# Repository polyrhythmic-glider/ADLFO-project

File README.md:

# Adolfo

Piattaforma Eurorack programmabile da 20 HP: quattro ingressi universali,
quattro uscite universali e quattro porte di controllo bidirezionali.
Quattro encoder con click, quattro tasti e OLED. Alimentazione Eurorack IDC10 ±12 V.

| Porta | Funzioni previste |
| --- | --- |
| IN1–4 | audio, CV, gate, trigger |
| OUT1–4 | audio, CV, envelope, LFO, gate, trigger |
| CTRL1–4 | CV/gate/trigger, ingresso oppure uscita |

## Due stati distinti

- **[Adolfo/](Adolfo/README.md)** è il firmware funzionante del prototipo
  Daisy + DAC Adafruit MCP4728, rinominato da DaisyMonoEnvelope. Motori e
  comandi sono conservati; il nome del binario diventa `Adolfo.bin`.
- **[hardware/pcb/](hardware/pcb/README.md)** contiene la nuova revisione D:
  schema gerarchico, filtri analogici, supervisione e due PCB con conversione
  esterna DC coupled. I rapporti CAD sono in `hardware/pcb/output/`.
  Il firmware del prototipo non pilota questa scheda: backend e qualifica
  al banco restano necessari prima dell'uso.

La [revisione completa del branch 20 HP](hardware/pcb/DESIGN_REVIEW_20HP.md)
individua inoltre blocchi di progetto su sequenziamento dell'ADC, supervisione
5 V e backend SPI/DMA. Lo stato CAD superato non autorizza il rilascio hardware.

Le vecchie PCB 24/20 HP per il solo AD/LFO, le diagnostiche separate e gli
schemi breadboard superati sono stati rimossi dal branch. La storia Git conserva
il materiale precedente; [pulizia e conservazione](docs/CLEANUP.md).

## Da dove iniziare

1. [Architettura e compromessi](hardware/pcb/ARCHITECTURE.md).
2. [Componenti da aggiungere e materiale da riutilizzare](hardware/pcb/PARTS.md).
3. [Cablaggio del prototipo preservato](docs/PROTOTYPE.md).
4. [Lavoro restante prima della produzione](hardware/pcb/RELEASE_CHECKLIST.md).

## Generazione e controlli

Python 3 con venv, compilatore C++ per i test locali. I file hardware sono
verificati con KiCad 10.0.7. Per aprirli e ricostruirli seguire le
[istruzioni hardware](hardware/pcb/README.md): `make pcb` da solo rigenera
il posizionamento e sostituisce le piste; non completa il processo di routing.

```sh
python3 -m venv .venv
.venv/bin/python -m pip install -r hardware/pcb/requirements.txt
make check
make test
```

Per il firmware del prototipo servono libDaisy/DaisySP e `arm-none-eabi`:

```sh
make -C Adolfo
make -C Adolfo test
```

I percorsi delle librerie restano sovrascrivibili con `LIBDAISY_DIR` e
`DAISYSP_DIR`. Nessun comando di generazione carica firmware o ordina una PCB.

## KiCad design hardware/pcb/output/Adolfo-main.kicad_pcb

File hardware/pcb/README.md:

# Adolfo universal — revisione D

Due PCB per un modulo Eurorack da 20 HP: 4 IN, 4 OUT, 4 CTRL bidirezionali,
quattro encoder con click, quattro tasti e OLED. La revisione D completa lo schema
funzionale, i filtri, l'alimentazione, la supervisione e le piste delle due schede.

**Alimentazione dal connettore Eurorack IDC10, senza USB-C:** il +12 V del case,
attraverso fusibile e protezione di polarità, alimenta il convertitore RECOM a 5 V.
Questi 5 V alimentano VIN della Daisy (pin 39) e il ramo analogico filtrato;
la Daisy genera i 3,3 V. Il −12 V alimenta il ramo analogico negativo.
Non serve il +5 V del case. Lasciare scollegata la USB-C della Seed nel modulo
assemblato: la Seed standard può alimentarsi da USB e il carrier non interrompe
quel percorso interno. Per programmare via USB, estrarre la Seed dal carrier
con il case spento e scollegato.

**Rilascio bloccato dalla [revisione completa](DESIGN_REVIEW_20HP.md):** sequenziamento
AVCC/VDRIVE dell'ADC, margini del monitor 5 V e backend SPI/DMA da riprogettare.
Il superamento dei controlli CAD non risolve questi problemi elettrici.
I datasheet consultati sono conservati localmente in `datasheets/`;
`references.json` registra le fonti e la revisione riporta le basi di verifica.

Aprire con **KiCad 10**:

- [output/Adolfo-main.kicad_pro](output/Adolfo-main.kicad_pro): progetto principale, schema gerarchico e PCB a quattro strati.
- [output/Adolfo-panel.kicad_pro](output/Adolfo-panel.kicad_pro): comandi, jack, display e PCB frontale a due strati.
- [output/index.html](output/index.html): viste 2D e distinta ricercabile.
- [output/front.svg](output/front.svg): frontale aggiornato con display centrale.
- [output/drill.svg](output/drill.svg) e [DXF](output/panel-concept.dxf): dima e taglio nominali aggiornati.
- [output/bom.csv](output/bom.csv): valori, codici scelti, lato e coordinate.
- [output/validation.json](output/validation.json): esito dei controlli sulla revisione salvata.

Le librerie locali sono incluse: tenere tutta la cartella `output` insieme.
Le viste correnti sono SVG; le vecchie copie PNG/PDF della revisione C e la
netlist unica del vecchio progetto sono state rimosse. Le netlist native correnti
sono `Adolfo-main.net` e `Adolfo-panel.net`.
In KiCad, dal gestore progetto aprire lo schema oppure l'editor PCB. Le piste
visibili nell'editor sono rame reale del file PCB. Non è inclusa un'immagine 3D.

La qualifica CAD comprende ERC, DRC, collegamenti mancanti e parità schema/PCB,
oltre al confronto pin per pin fra sorgente, netlist compilata e schede salvate.
I rapporti nativi sono `erc-main.json`, `erc-panel.json`, `drc-main.json` e
`drc-panel.json`. `native-checks.json` ne registra le impronte SHA256, insieme
ai file CAD verificati: una modifica richiede nuovi controlli.

**Prototipo ingegneristico, non ancora qualificato al banco.** Il firmware in
`Adolfo/` pilota il vecchio prototipo con MCP4728; per questa PCB occorre il
backend ADC/DAC, il filtro digitale e il collaudo indicato nella
[lista di qualifica](RELEASE_CHECKLIST.md). Non confondere DRC pulito con misura
di rumore, stabilità, termica o precisione sotto carico.

[Architettura](ARCHITECTURE.md) · [Componenti e montaggio](PARTS.md)

## Rigenerazione

La generazione iniziale **sostituisce le schede e rimuove lo sbroglio esistente**.
Usarla solo quando si intende ricostruire la revisione, conservando prima il lavoro.
Servono Python con `requirements.txt`, KiCad 10 e Java 21 con
[Freerouting 2.0.1](https://github.com/freerouting/freerouting/releases/tag/v2.0.1).
Il JAR va in `.venv/tools/freerouting-2.0.1.jar` oppure in `FREEROUTING_JAR`.
Il router lavora localmente, con telemetria disattivata (`-da`).

PowerShell, dalla radice del repository:

```powershell
& .\.venv\Scripts\python.exe -X utf8 hardware/pcb/build.py
& 'C:\Program Files\KiCad\10.0\bin\python.exe' -X utf8 hardware/pcb/board_setup.py
& 'C:\Program Files\KiCad\10.0\bin\python.exe' -X utf8 hardware/pcb/route.py
& .\.venv\Scripts\python.exe -X utf8 hardware/pcb/native_checks.py
& 'C:\Program Files\KiCad\10.0\bin\python.exe' -X utf8 hardware/pcb/board_setup.py audit
& .\.venv\Scripts\python.exe -X utf8 hardware/pcb/validate.py
```

Per ricontrollare i file esistenti eseguire solo gli ultimi tre comandi.
`build.py` genera schema, impronte, distinta e posizionamento; `board_setup.py`
compila le netlist, applica i lati, configura gli strati, collega i pad di massa al piano con vie fisiche e crea i DSN. `route.py`
importa una nuova sessione solo dopo che il router termina correttamente.
`native_checks.py` richiede zero segnalazioni, senza esclusioni DRC, ed esporta quattro viste SVG del rame.
`validate.py` rifiuta rapporti o audit riferiti a file precedenti.

I file DSN/SES intermedi restano nella cartella ignorata `build/`. Il router
può lasciare connessioni aperte: la revisione consegnata comprende la chiusura
finale delle reti di alimentazione e supera i controlli. Dopo una rigenerazione
ricontrollare il risultato e completare eventuali reti residue in KiCad; il
validatore rifiuta uno sbroglio parziale. I file `.kicad_pcb` salvati sono il
risultato completo da aprire e modificare. I disegni meccanici hanno quote nominali e
richiedono una prova fisica prima di forare il frontale definitivo.

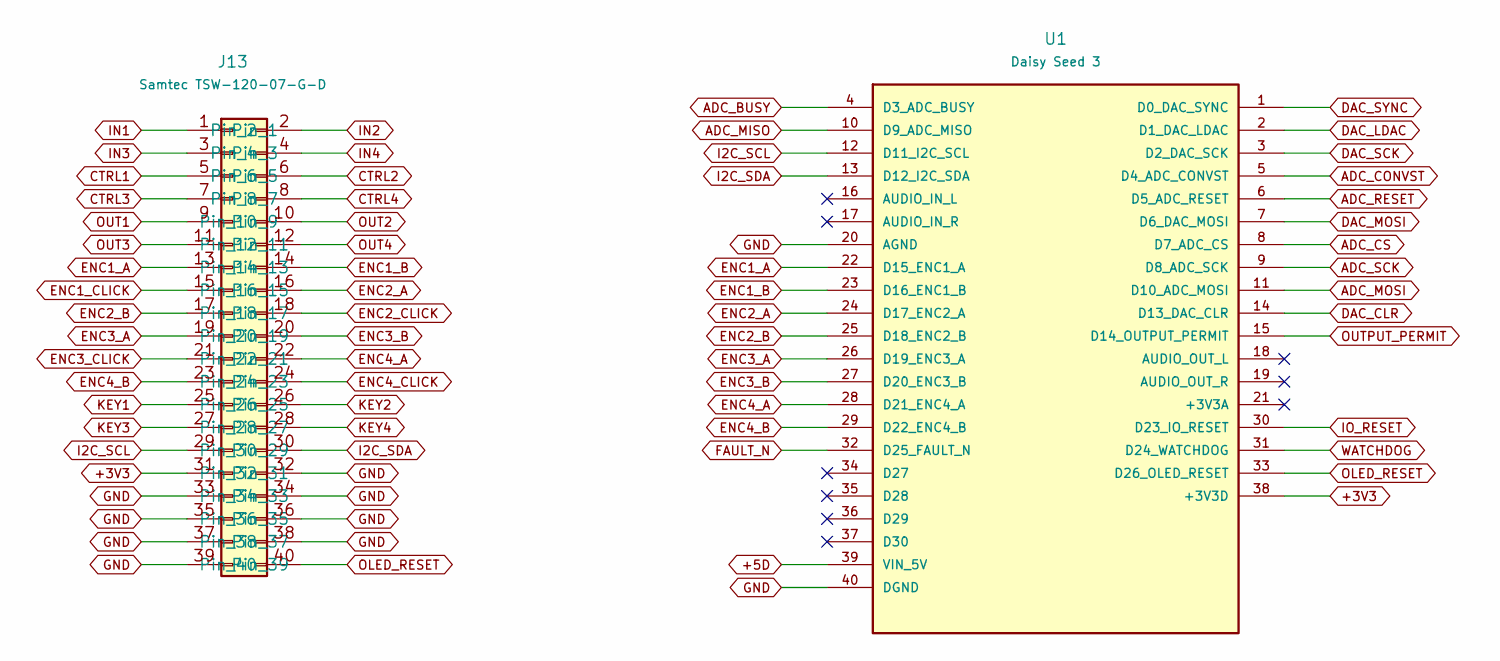
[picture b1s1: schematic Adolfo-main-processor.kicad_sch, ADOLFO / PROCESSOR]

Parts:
J13: Samtec TSW-120-07-G-D; header40
U1: Daisy Seed 3; seed

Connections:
+3V3: J13.31, U1.38 (+3V3D); also elsewhere on the board
+5D: U1.39 (VIN_5V); also elsewhere on the board
ADC_BUSY: U1.4 (D3_ADC_BUSY); also elsewhere on the board
ADC_CONVST: U1.5 (D4_ADC_CONVST); also elsewhere on the board
ADC_CS: U1.8 (D7_ADC_CS); also elsewhere on the board
ADC_MISO: U1.10 (D9_ADC_MISO); also elsewhere on the board
ADC_MOSI: U1.11 (D10_ADC_MOSI); also elsewhere on the board
ADC_RESET: U1.6 (D5_ADC_RESET); also elsewhere on the board
ADC_SCK: U1.9 (D8_ADC_SCK); also elsewhere on the board
CTRL1: J13.5; also elsewhere on the board
CTRL2: J13.6; also elsewhere on the board
CTRL3: J13.7; also elsewhere on the board
CTRL4: J13.8; also elsewhere on the board
DAC_CLR: U1.14 (D13_DAC_CLR); also elsewhere on the board
DAC_LDAC: U1.2 (D1_DAC_LDAC); also elsewhere on the board
DAC_MOSI: U1.7 (D6_DAC_MOSI); also elsewhere on the board
DAC_SCK: U1.3 (D2_DAC_SCK); also elsewhere on the board
DAC_SYNC: U1.1 (D0_DAC_SYNC); also elsewhere on the board
ENC1_A: J13.13, U1.22 (D15_ENC1_A); also elsewhere on the board
ENC1_B: J13.14, U1.23 (D16_ENC1_B); also elsewhere on the board
ENC1_CLICK: J13.15; also elsewhere on the board
ENC2_A: J13.16, U1.24 (D17_ENC2_A); also elsewhere on the board
ENC2_B: J13.17, U1.25 (D18_ENC2_B); also elsewhere on the board
ENC2_CLICK: J13.18; also elsewhere on the board
ENC3_A: J13.19, U1.26 (D19_ENC3_A); also elsewhere on the board
ENC3_B: J13.20, U1.27 (D20_ENC3_B); also elsewhere on the board
ENC3_CLICK: J13.21; also elsewhere on the board
ENC4_A: J13.22, U1.28 (D21_ENC4_A); also elsewhere on the board
ENC4_B: J13.23, U1.29 (D22_ENC4_B); also elsewhere on the board
ENC4_CLICK: J13.24; also elsewhere on the board
FAULT_N: U1.32 (D25_FAULT_N); also elsewhere on the board
GND: J13.32, J13.33, J13.34, J13.35, J13.36, J13.37, J13.38, J13.39, U1.20 (AGND), U1.40 (DGND); also elsewhere on the board
I2C_SCL: J13.29, U1.12 (D11_I2C_SCL); also elsewhere on the board
I2C_SDA: J13.30, U1.13 (D12_I2C_SDA); also elsewhere on the board
IN1: J13.1; also elsewhere on the board
IN2: J13.2; also elsewhere on the board
IN3: J13.3; also elsewhere on the board
IN4: J13.4; also elsewhere on the board
IO_RESET: U1.30 (D23_IO_RESET); also elsewhere on the board
KEY1: J13.25; also elsewhere on the board
KEY2: J13.26; also elsewhere on the board
KEY3: J13.27; also elsewhere on the board
KEY4: J13.28; also elsewhere on the board
OLED_RESET: J13.40, U1.33 (D26_OLED_RESET); also elsewhere on the board
OUT1: J13.9; also elsewhere on the board
OUT2: J13.10; also elsewhere on the board
OUT3: J13.11; also elsewhere on the board
OUT4: J13.12; also elsewhere on the board
OUTPUT_PERMIT: U1.15 (D14_OUTPUT_PERMIT); also elsewhere on the board
WATCHDOG: U1.31 (D24_WATCHDOG); also elsewhere on the board

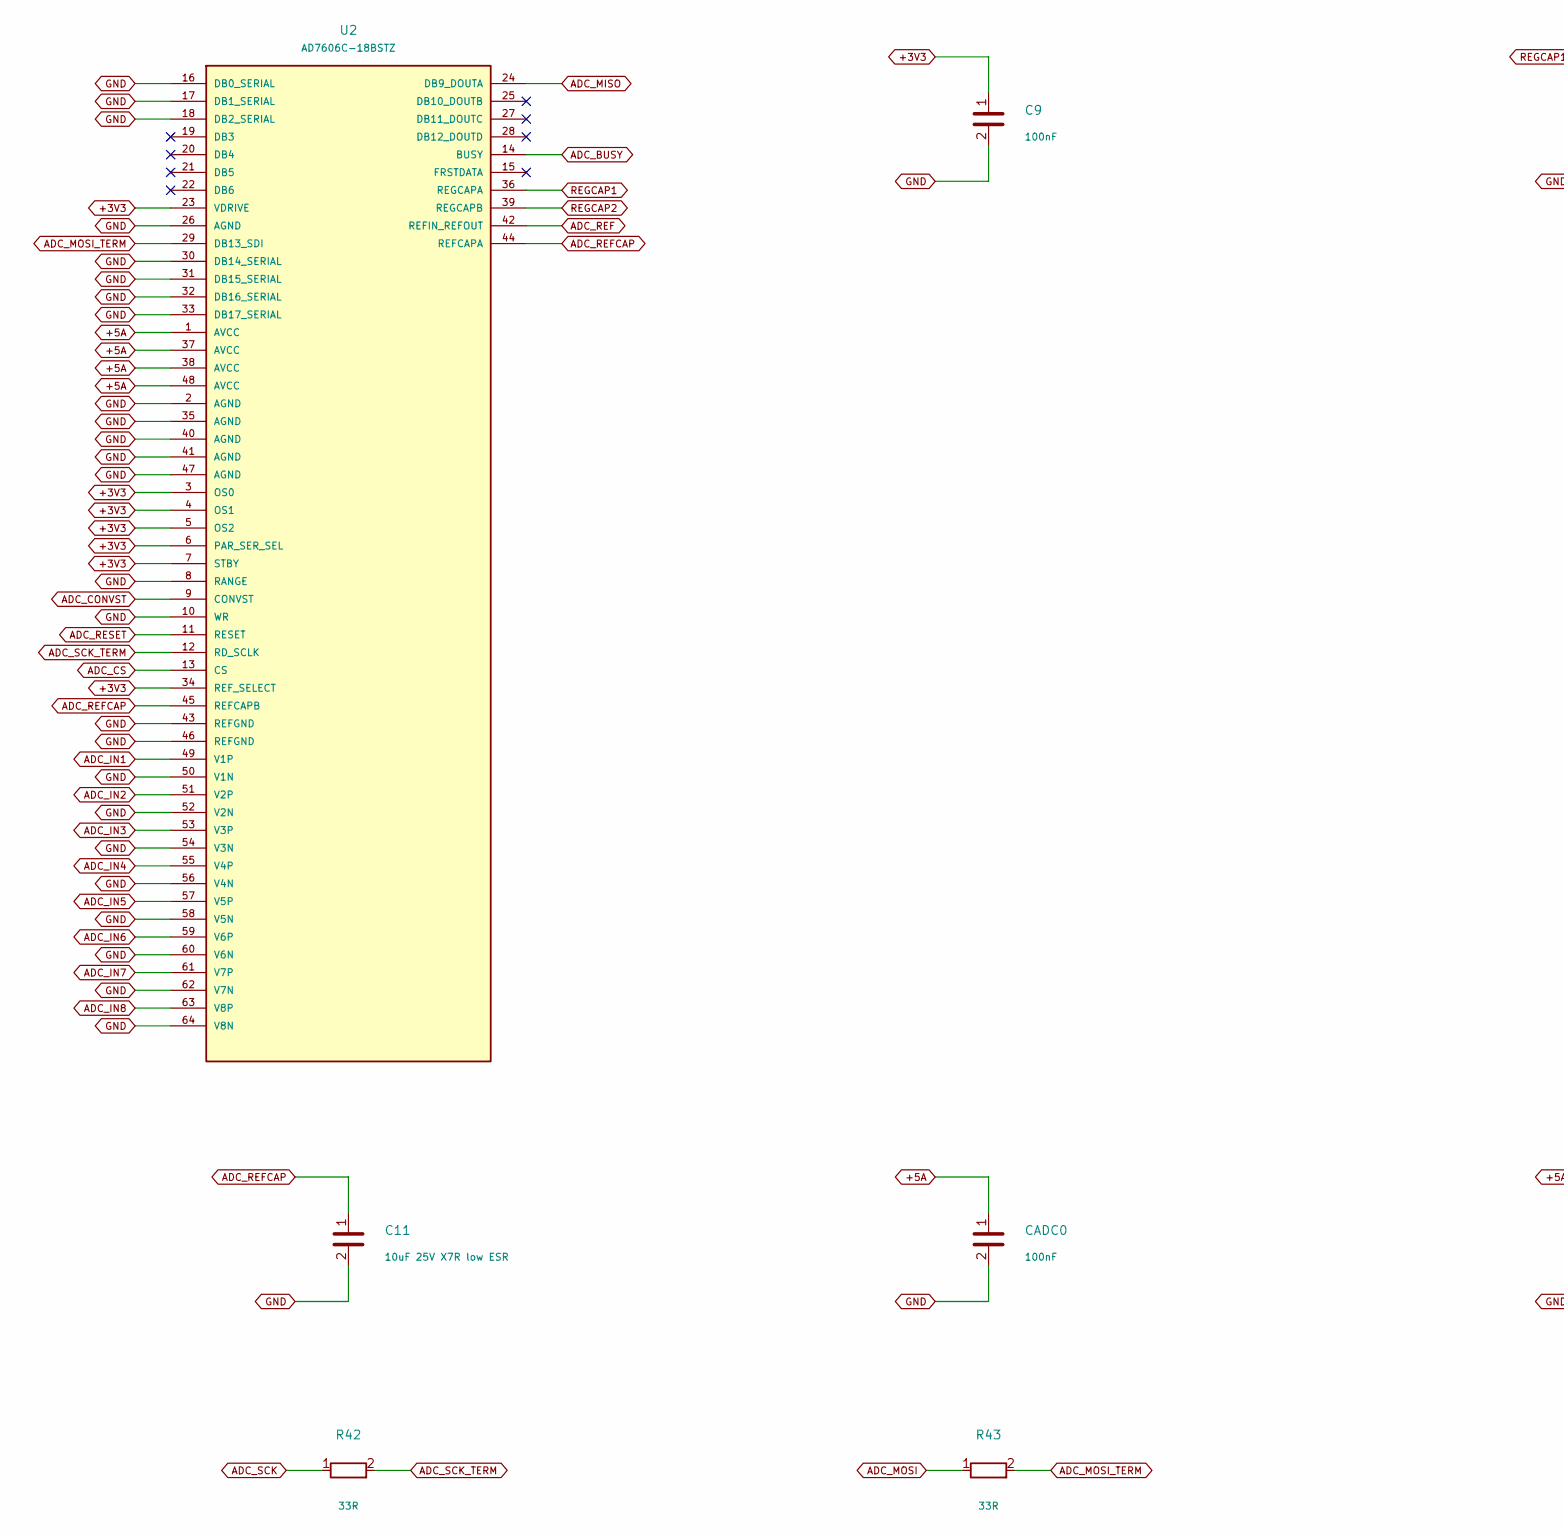
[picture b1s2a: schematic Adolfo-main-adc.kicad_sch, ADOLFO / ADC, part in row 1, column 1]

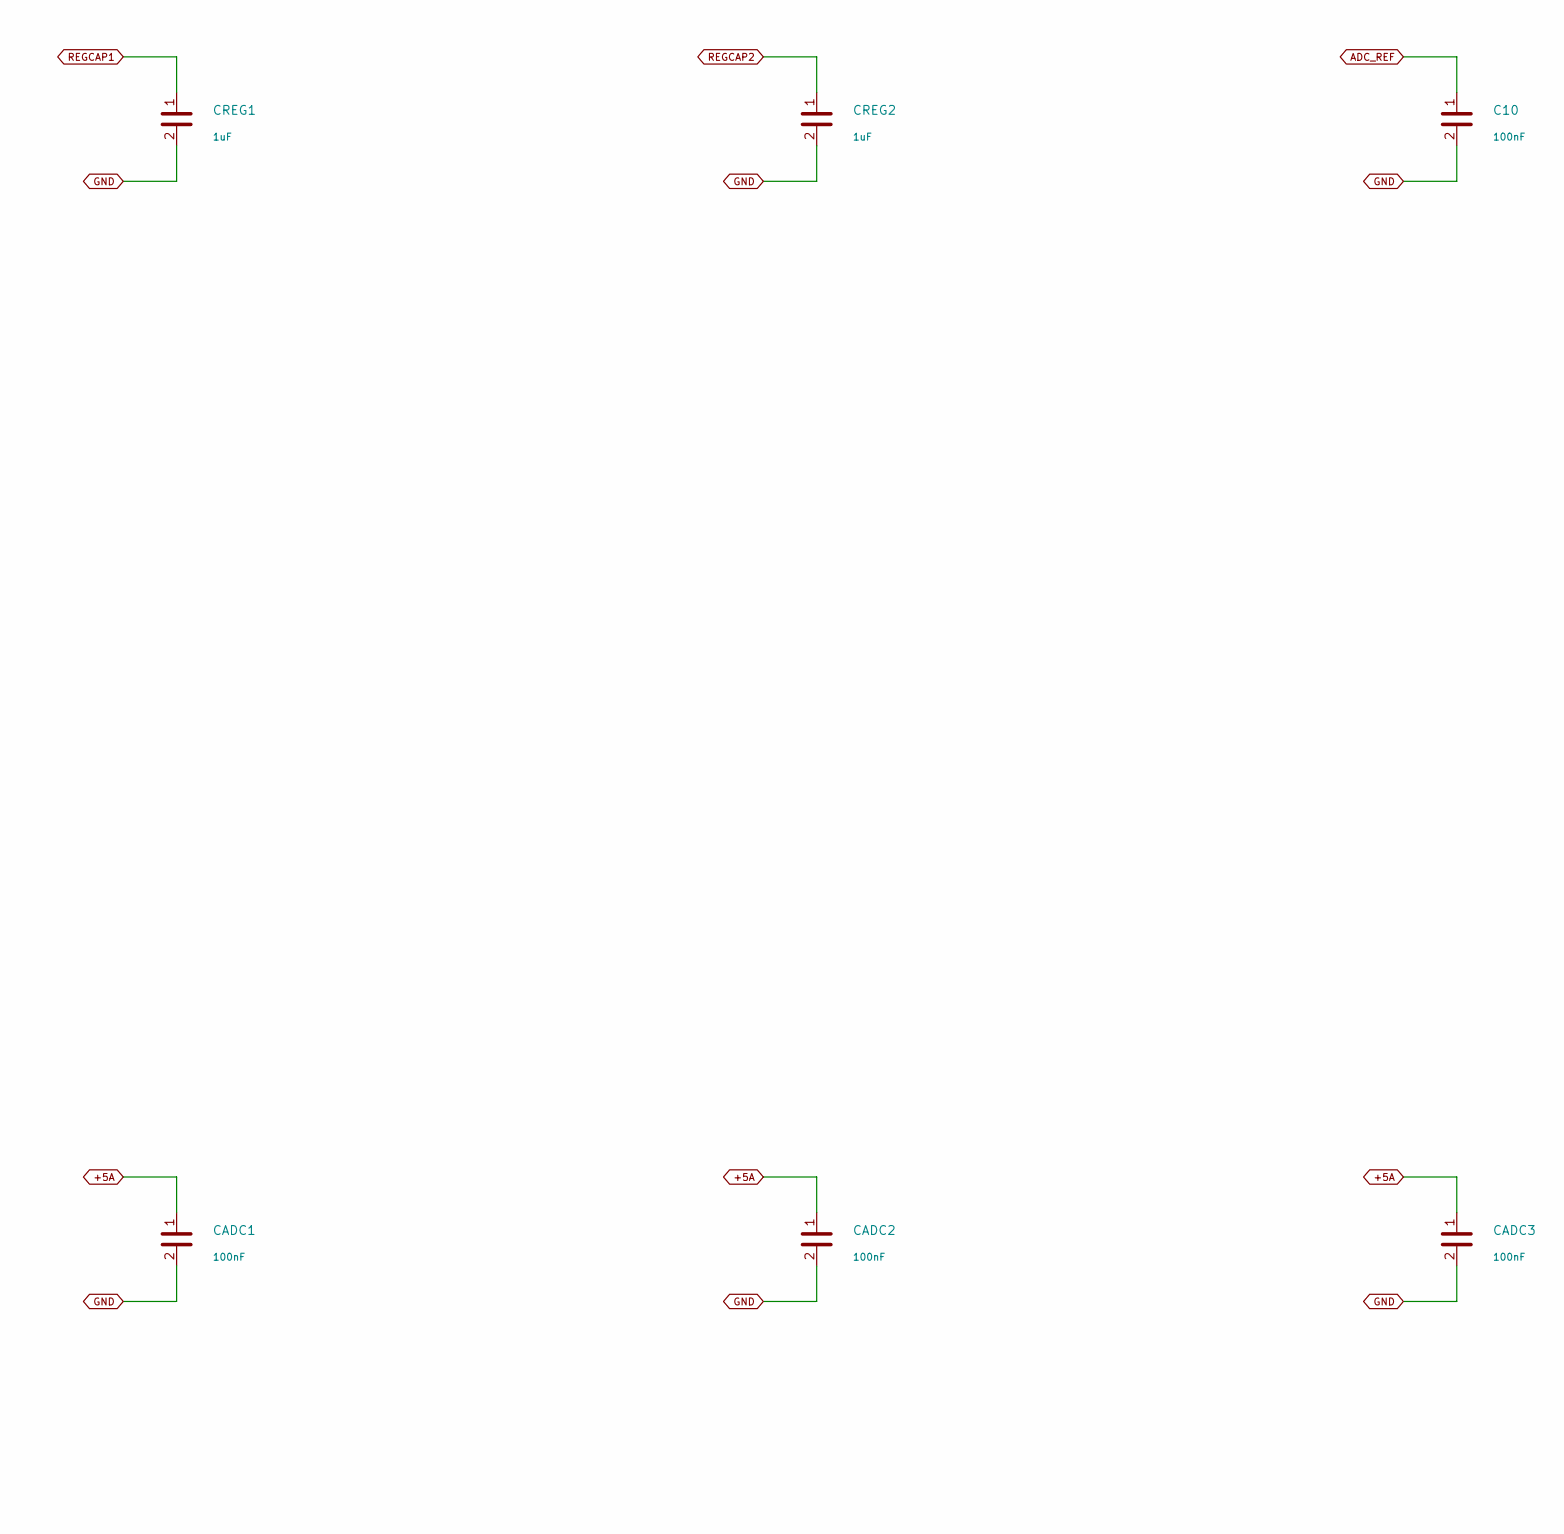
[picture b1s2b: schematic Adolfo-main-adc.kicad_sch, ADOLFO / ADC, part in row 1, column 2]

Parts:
C9, C10: 100nF; c0603
C11: 10uF 25V X7R low ESR; c1210
CADC0, CADC1, CADC2, CADC3: 100nF; c0603
CREG1, CREG2: 1uF; c0603
R42, R43: 33R; r0805
U2: AD7606C-18BSTZ; lqfp64; MPN AD7606C-18BSTZ

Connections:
+3V3: C9.1, U2.3 (OS0), U2.4 (OS1), U2.5 (OS2), U2.6 (PAR_SER_SEL), U2.7 (STBY), U2.23 (VDRIVE), U2.34 (REF_SELECT); also elsewhere on the board
+5A: CADC0.1, CADC1.1, CADC2.1, CADC3.1, U2.1 (AVCC), U2.37 (AVCC), U2.38 (AVCC), U2.48 (AVCC); also elsewhere on the board
ADC_BUSY: U2.14 (BUSY); also elsewhere on the board
ADC_CONVST: U2.9 (CONVST); also elsewhere on the board
ADC_CS: U2.13 (CS); also elsewhere on the board
ADC_IN1: U2.49 (V1P); also elsewhere on the board
ADC_IN2: U2.51 (V2P); also elsewhere on the board
ADC_IN3: U2.53 (V3P); also elsewhere on the board
ADC_IN4: U2.55 (V4P); also elsewhere on the board
ADC_IN5: U2.57 (V5P); also elsewhere on the board
ADC_IN6: U2.59 (V6P); also elsewhere on the board
ADC_IN7: U2.61 (V7P); also elsewhere on the board
ADC_IN8: U2.63 (V8P); also elsewhere on the board
ADC_MISO: U2.24 (DB9_DOUTA); also elsewhere on the board
ADC_MOSI: R43.1; also elsewhere on the board
ADC_MOSI_TERM: R43.2, U2.29 (DB13_SDI)
ADC_REF: C10.1, U2.42 (REFIN_REFOUT)
ADC_REFCAP: C11.1, U2.44 (REFCAPA), U2.45 (REFCAPB)
ADC_RESET: U2.11 (RESET); also elsewhere on the board
ADC_SCK: R42.1; also elsewhere on the board
ADC_SCK_TERM: R42.2, U2.12 (RD_SCLK)
GND: C9.2, C10.2, C11.2, CADC0.2, CADC1.2, CADC2.2, CADC3.2, CREG1.2, CREG2.2, U2.2 (AGND), U2.8 (RANGE), U2.10 (WR), U2.16 (DB0_SERIAL), U2.17 (DB1_SERIAL), U2.18 (DB2_SERIAL), U2.26 (AGND), U2.30 (DB14_SERIAL), U2.31 (DB15_SERIAL), U2.32 (DB16_SERIAL), U2.33 (DB17_SERIAL), U2.35 (AGND), U2.40 (AGND), U2.41 (AGND), U2.43 (REFGND), U2.46 (REFGND), U2.47 (AGND), U2.50 (V1N), U2.52 (V2N), U2.54 (V3N), U2.56 (V4N), U2.58 (V5N), U2.60 (V6N), U2.62 (V7N), U2.64 (V8N); also elsewhere on the board
REGCAP1: CREG1.1, U2.36 (REGCAPA)
REGCAP2: CREG2.1, U2.39 (REGCAPB)

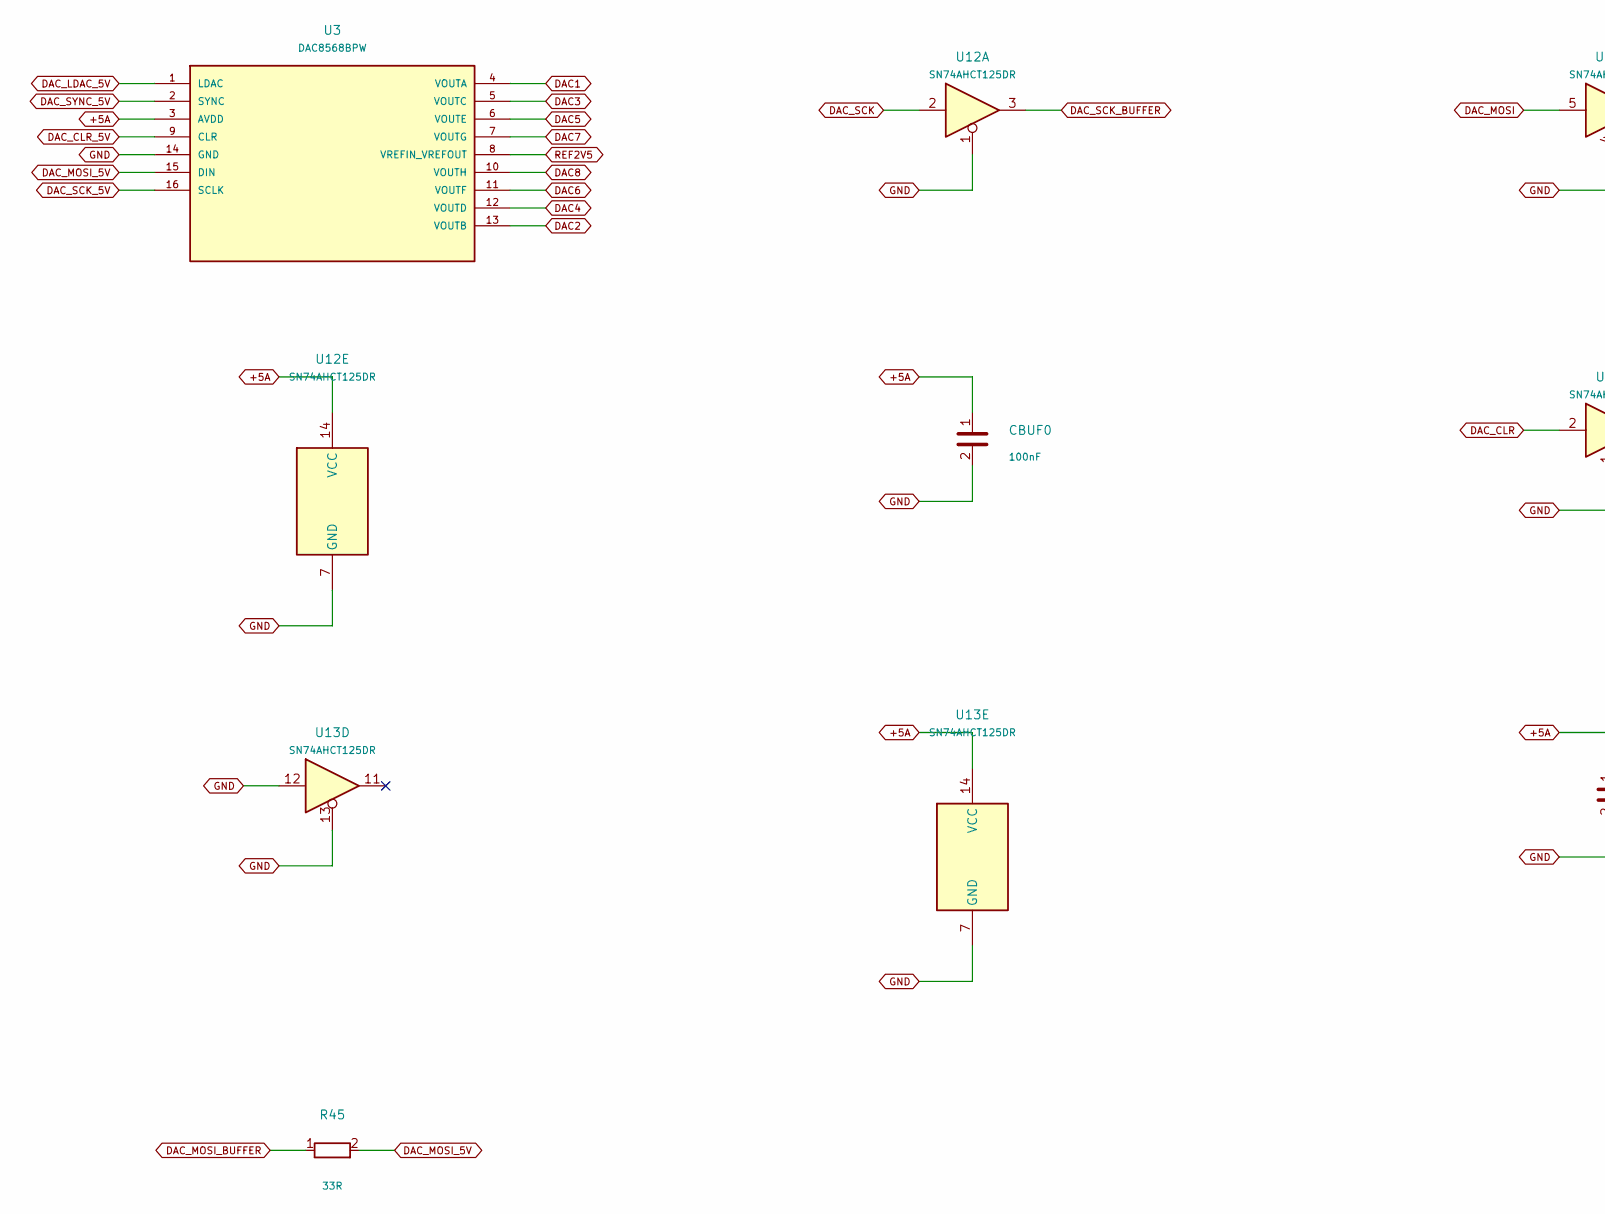
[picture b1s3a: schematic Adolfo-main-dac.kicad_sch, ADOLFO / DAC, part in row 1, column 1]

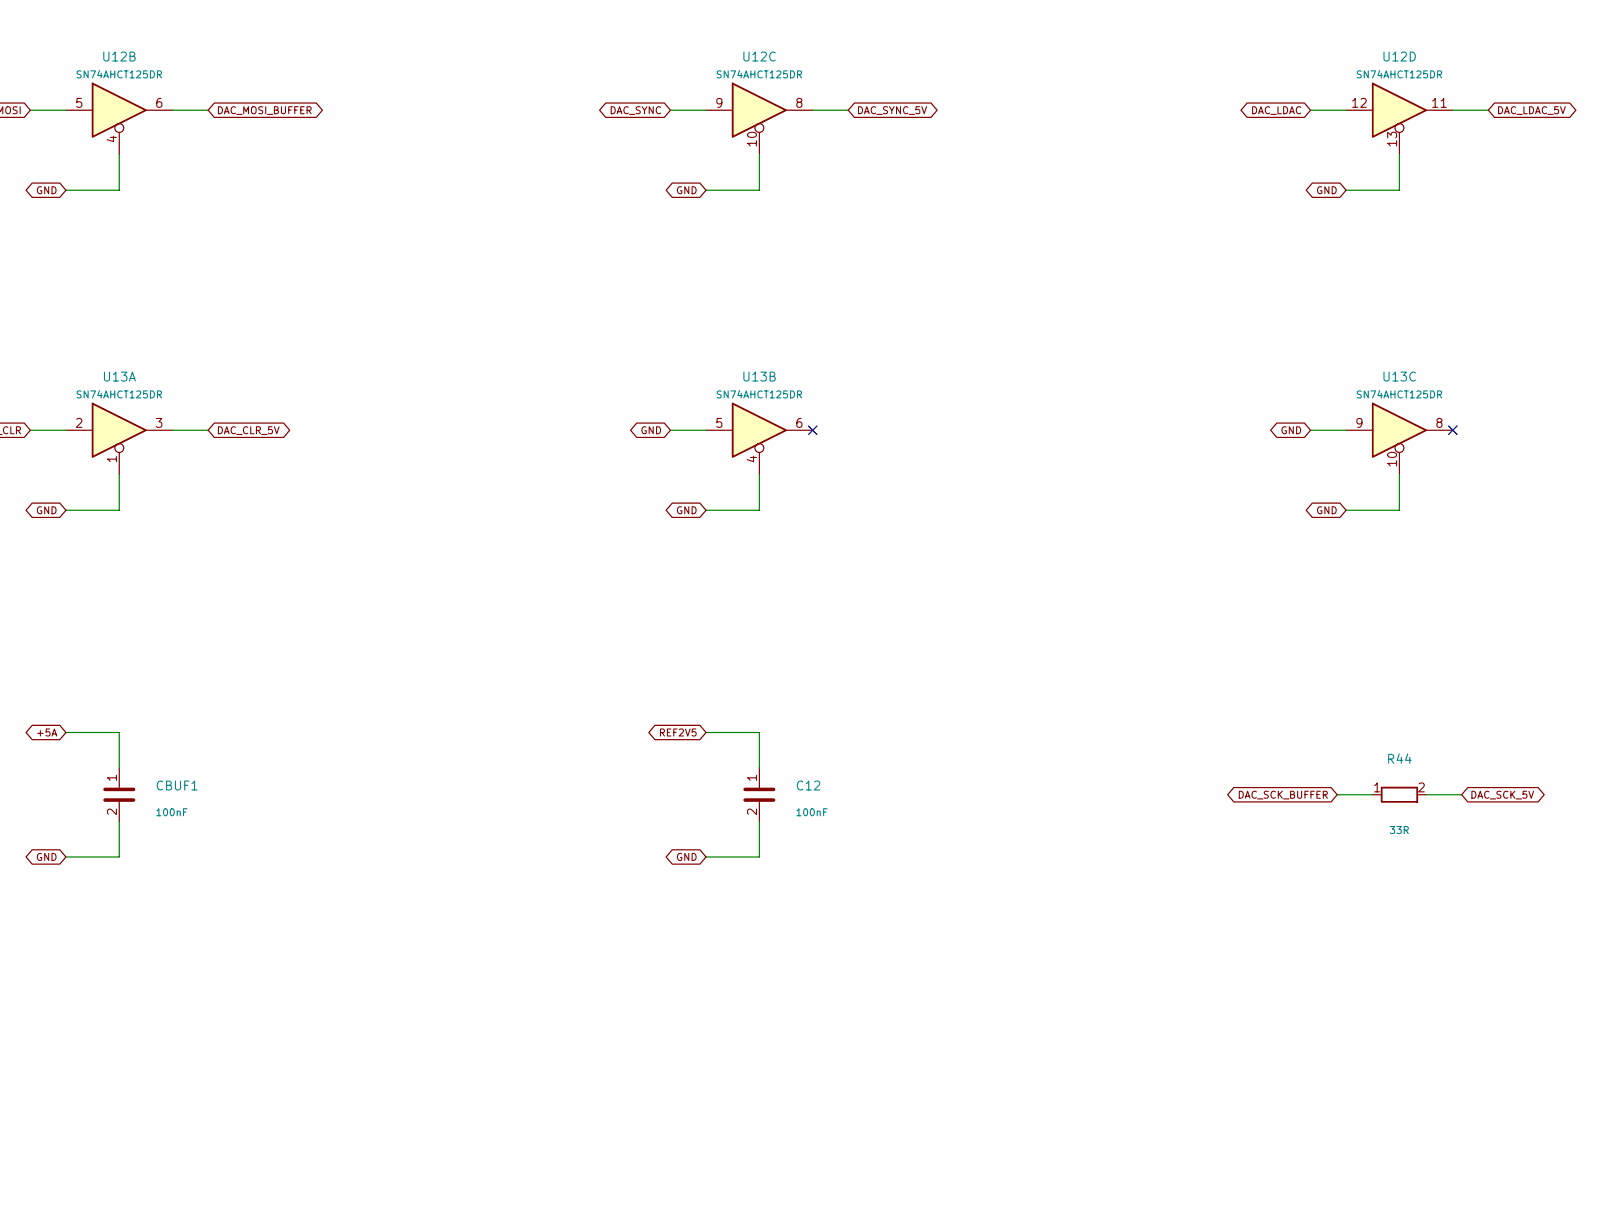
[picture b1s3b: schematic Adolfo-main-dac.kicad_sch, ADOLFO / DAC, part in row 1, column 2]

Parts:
C12: 100nF; c0805
CBUF0, CBUF1: 100nF; c0805
R44, R45: 33R; r0805
U3: DAC8568BPW; tssop16; MPN DAC8568BPW
U12, U13: SN74AHCT125DR; soic14; MPN SN74AHCT125DR

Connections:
+5A: CBUF0.1, CBUF1.1, U3.3 (AVDD), U12.14 (VCC), U13.14 (VCC); also elsewhere on the board
DAC1: U3.4 (VOUTA); also elsewhere on the board
DAC2: U3.13 (VOUTB); also elsewhere on the board
DAC3: U3.5 (VOUTC); also elsewhere on the board
DAC4: U3.12 (VOUTD); also elsewhere on the board
DAC5: U3.6 (VOUTE); also elsewhere on the board
DAC6: U3.11 (VOUTF); also elsewhere on the board
DAC7: U3.7 (VOUTG); also elsewhere on the board
DAC8: U3.10 (VOUTH); also elsewhere on the board
DAC_CLR: U13.2; also elsewhere on the board
DAC_CLR_5V: U3.9 (CLR), U13.3
DAC_LDAC: U12.12; also elsewhere on the board
DAC_LDAC_5V: U3.1 (LDAC), U12.11
DAC_MOSI: U12.5; also elsewhere on the board
DAC_MOSI_5V: R45.2, U3.15 (DIN)
DAC_MOSI_BUFFER: R45.1, U12.6
DAC_SCK: U12.2; also elsewhere on the board
DAC_SCK_5V: R44.2, U3.16 (SCLK)
DAC_SCK_BUFFER: R44.1, U12.3
DAC_SYNC: U12.9; also elsewhere on the board
DAC_SYNC_5V: U3.2 (SYNC), U12.8
GND: C12.2, CBUF0.2, CBUF1.2, U3.14 (GND), U12.1, U12.4, U12.7 (GND), U12.10, U12.13, U13.1, U13.4, U13.5, U13.7 (GND), U13.9, U13.10, U13.12, U13.13; also elsewhere on the board
REF2V5: C12.1, U3.8 (VREFIN_VREFOUT); also elsewhere on the board

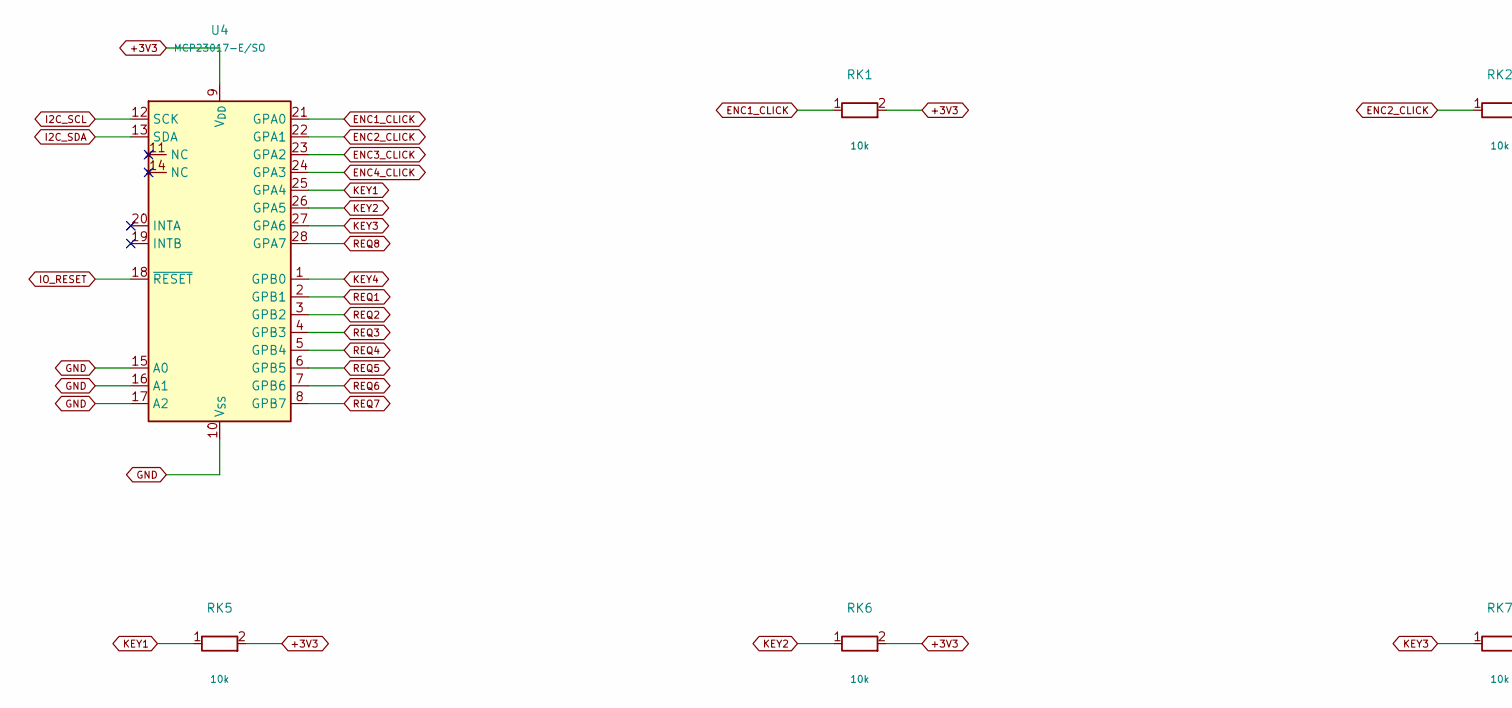
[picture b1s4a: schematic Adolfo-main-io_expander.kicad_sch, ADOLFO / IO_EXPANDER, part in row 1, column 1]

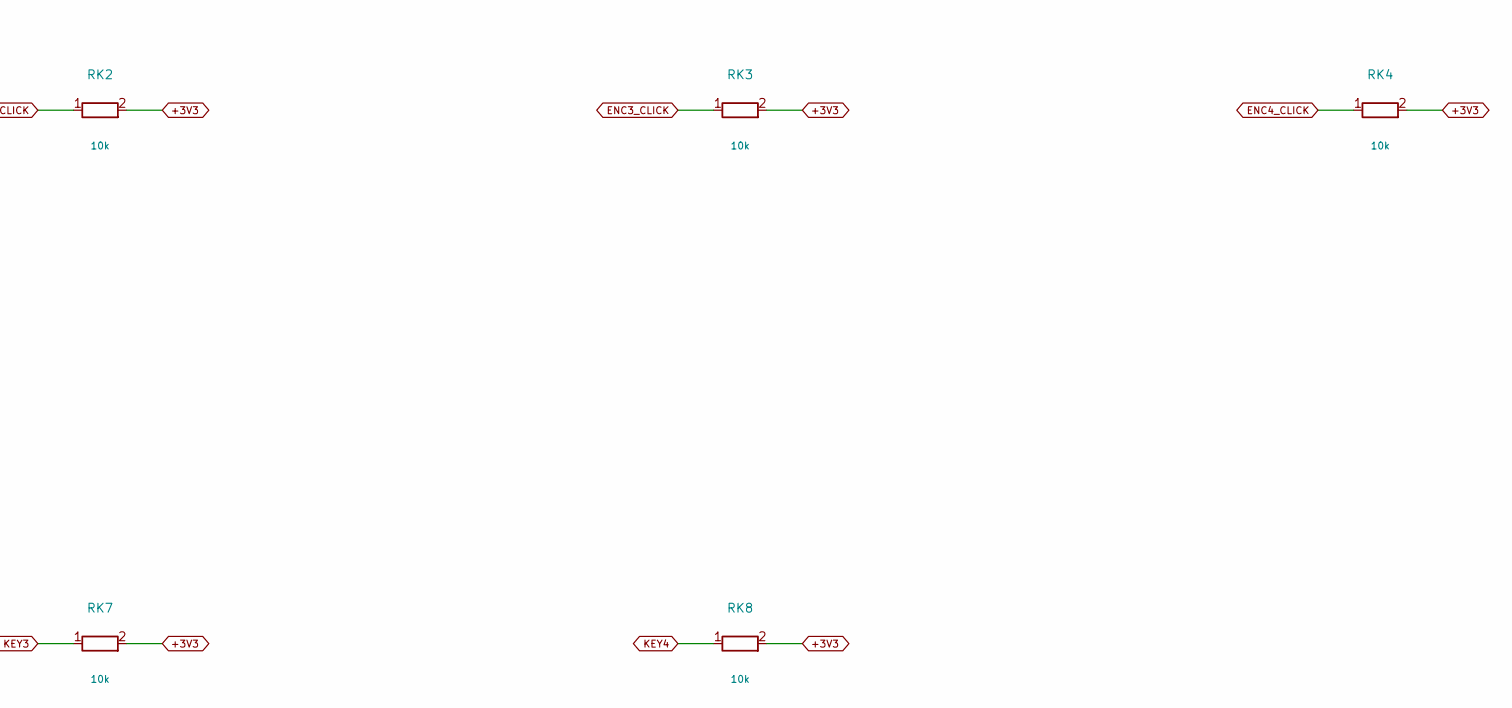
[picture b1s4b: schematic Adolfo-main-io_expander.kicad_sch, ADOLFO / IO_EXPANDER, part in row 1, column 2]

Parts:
RK1, RK2, RK3, RK4, RK5, RK6, RK7, RK8: 10k; r0805
U4: MCP23017-E/SO; soic28; MPN MCP23017-E/SO

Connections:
+3V3: RK1.2, RK2.2, RK3.2, RK4.2, RK5.2, RK6.2, RK7.2, RK8.2, U4.9 (V_{DD}); also elsewhere on the board
ENC1_CLICK: RK1.1, U4.21 (GPA0); also elsewhere on the board
ENC2_CLICK: RK2.1, U4.22 (GPA1); also elsewhere on the board
ENC3_CLICK: RK3.1, U4.23 (GPA2); also elsewhere on the board
ENC4_CLICK: RK4.1, U4.24 (GPA3); also elsewhere on the board
GND: U4.10 (V_{SS}), U4.15 (A0), U4.16 (A1), U4.17 (A2); also elsewhere on the board
I2C_SCL: U4.12 (SCK); also elsewhere on the board
I2C_SDA: U4.13 (SDA); also elsewhere on the board
IO_RESET: U4.18 (~RESET); also elsewhere on the board
KEY1: RK5.1, U4.25 (GPA4); also elsewhere on the board
KEY2: RK6.1, U4.26 (GPA5); also elsewhere on the board
KEY3: RK7.1, U4.27 (GPA6); also elsewhere on the board
KEY4: RK8.1, U4.1 (GPB0); also elsewhere on the board
REQ1: U4.2 (GPB1); also elsewhere on the board
REQ2: U4.3 (GPB2); also elsewhere on the board
REQ3: U4.4 (GPB3); also elsewhere on the board
REQ4: U4.5 (GPB4); also elsewhere on the board
REQ5: U4.6 (GPB5); also elsewhere on the board
REQ6: U4.7 (GPB6); also elsewhere on the board
REQ7: U4.8 (GPB7); also elsewhere on the board
REQ8: U4.28 (GPA7); also elsewhere on the board
